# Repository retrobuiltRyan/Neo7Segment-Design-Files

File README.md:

KiCAD 8.x files created.

A reworked layout of Unexpected Maker's 7SegNeo Display project. Chain these addressable LED modules together to make a large 7-segment display. Control via any micro-controller just like you would control a strip of RGB LEDs. Custom library made by Unexpected Maker.

Assembly Required:
Each moduled has a resistor footprint at the Data In line. The first module in the chain requires a ~220-330 ohm resistor soldered here. Each moduled next in the chain requires this jumper closed; 0-ohm resistor or just a solder blob.

Change list: bumped-up passives footprint to 1206, finessed trace/ copper pour layout; slightly larger PCB area, larger mounting holes, decimal place pixel same footprint as all other pixels.
Created some 3D printable mounting brackets to expidite building projects like a clock/scoreboard. 

RGBLEDs: 1568-16347CT-ND or https://www.aliexpress.us/item/3256802466699315.html

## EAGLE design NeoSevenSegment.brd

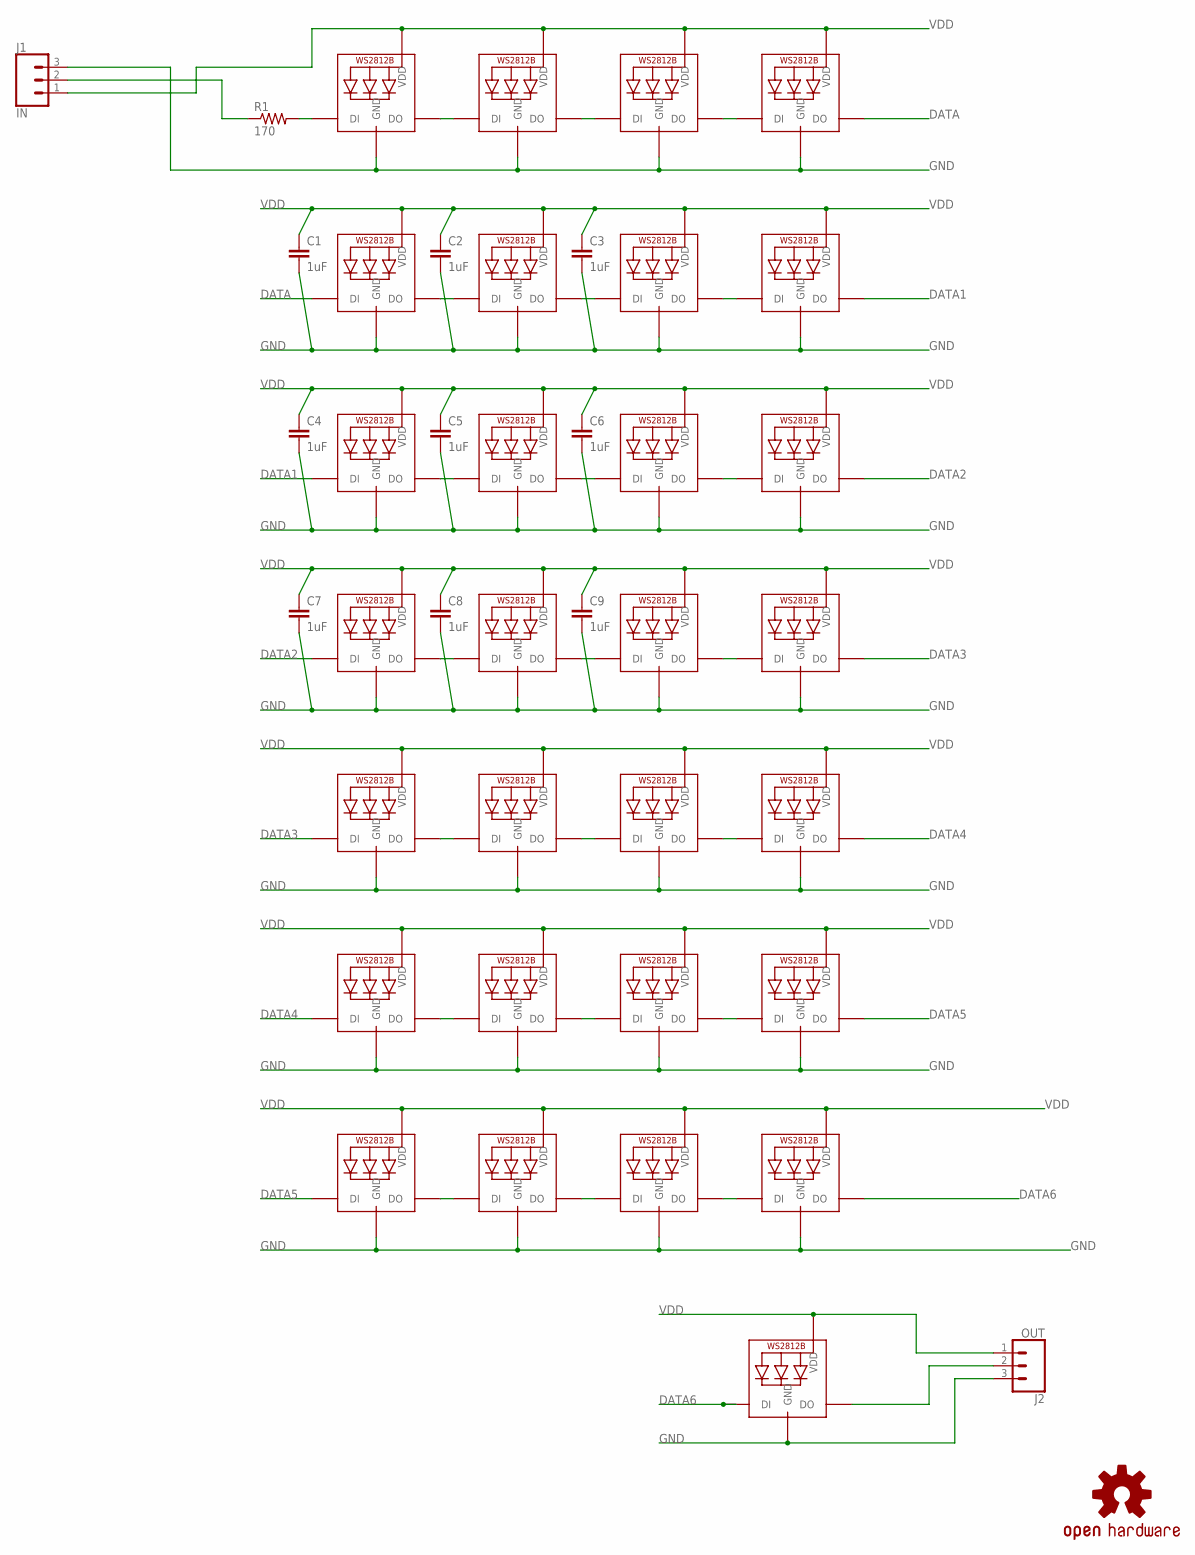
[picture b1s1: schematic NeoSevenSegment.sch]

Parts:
C1, C2, C3, C4, C5, C6, C7, C8, C9: 1uF; C1210
J1: IN; 1X03_LONGPADS
J2: OUT; 1X03_LONGPADS
LED1, LED2, LED3, LED4, LED5, LED6, LED7, LED8, LED9, LED10, LED11, LED12, LED13, LED14, LED15, LED16, LED17, LED18, LED19, LED20, LED21, LED22, LED23, LED24, LED25, LED26, LED27, LED28, LED29: WS2812B_5050N; WS2812B-NARROW
LOGO1: OSHW-LOGOM; OSHW-LOGO-M
R1: 170; R1206

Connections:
DATA: LED4.2-DOUT (DO), LED5.4-DIN (DI)
DATA1: LED8.2-DOUT (DO), LED9.4-DIN (DI)
DATA2: LED12.2-DOUT (DO), LED13.4-DIN (DI)
DATA3: LED16.2-DOUT (DO), LED17.4-DIN (DI)
DATA4: LED20.2-DOUT (DO), LED21.4-DIN (DI)
DATA5: LED24.2-DOUT (DO), LED25.4-DIN (DI)
DATA6: LED28.2-DOUT (DO), LED29.4-DIN (DI)
DATA_OUT: J2.2, LED29.2-DOUT (DO)
DI: J1.2, R1.1
DI_R: LED1.4-DIN (DI), R1.2
GND: C1.2, C2.2, C3.2, C4.2, C5.2, C6.2, C7.2, C8.2, C9.2, J1.3, J2.3, LED1.3-GND (GND), LED2.3-GND (GND), LED3.3-GND (GND), LED4.3-GND (GND), LED5.3-GND (GND), LED6.3-GND (GND), LED7.3-GND (GND), LED8.3-GND (GND), LED9.3-GND (GND), LED10.3-GND (GND), LED11.3-GND (GND), LED12.3-GND (GND), LED13.3-GND (GND), LED14.3-GND (GND), LED15.3-GND (GND), LED16.3-GND (GND), LED17.3-GND (GND), LED18.3-GND (GND), LED19.3-GND (GND), LED20.3-GND (GND), LED21.3-GND (GND), LED22.3-GND (GND), LED23.3-GND (GND), LED24.3-GND (GND), LED25.3-GND (GND), LED26.3-GND (GND), LED27.3-GND (GND), LED28.3-GND (GND), LED29.3-GND (GND)
unnamed: LED9.2-DOUT (DO), LED10.4-DIN (DI)
unnamed: LED10.2-DOUT (DO), LED11.4-DIN (DI)
unnamed: LED11.2-DOUT (DO), LED12.4-DIN (DI)
unnamed: LED1.2-DOUT (DO), LED2.4-DIN (DI)
unnamed: LED2.2-DOUT (DO), LED3.4-DIN (DI)
unnamed: LED3.2-DOUT (DO), LED4.4-DIN (DI)
unnamed: LED13.2-DOUT (DO), LED14.4-DIN (DI)
unnamed: LED14.2-DOUT (DO), LED15.4-DIN (DI)
unnamed: LED15.2-DOUT (DO), LED16.4-DIN (DI)
unnamed: LED17.2-DOUT (DO), LED18.4-DIN (DI)
unnamed: LED18.2-DOUT (DO), LED19.4-DIN (DI)
unnamed: LED5.2-DOUT (DO), LED6.4-DIN (DI)
unnamed: LED6.2-DOUT (DO), LED7.4-DIN (DI)
unnamed: LED7.2-DOUT (DO), LED8.4-DIN (DI)
unnamed: LED19.2-DOUT (DO), LED20.4-DIN (DI)
unnamed: LED21.2-DOUT (DO), LED22.4-DIN (DI)
unnamed: LED22.2-DOUT (DO), LED23.4-DIN (DI)
unnamed: LED23.2-DOUT (DO), LED24.4-DIN (DI)
S1: LED25.2-DOUT (DO), LED26.4-DIN (DI)
S2: LED26.2-DOUT (DO), LED27.4-DIN (DI)
S3: LED27.2-DOUT (DO), LED28.4-DIN (DI)
VDD: C1.1, C2.1, C3.1, C4.1, C5.1, C6.1, C7.1, C8.1, C9.1, J1.1, J2.1, LED1.1-VDD (VDD), LED2.1-VDD (VDD), LED3.1-VDD (VDD), LED4.1-VDD (VDD), LED5.1-VDD (VDD), LED6.1-VDD (VDD), LED7.1-VDD (VDD), LED8.1-VDD (VDD), LED9.1-VDD (VDD), LED10.1-VDD (VDD), LED11.1-VDD (VDD), LED12.1-VDD (VDD), LED13.1-VDD (VDD), LED14.1-VDD (VDD), LED15.1-VDD (VDD), LED16.1-VDD (VDD), LED17.1-VDD (VDD), LED18.1-VDD (VDD), LED19.1-VDD (VDD), LED20.1-VDD (VDD), LED21.1-VDD (VDD), LED22.1-VDD (VDD), LED23.1-VDD (VDD), LED24.1-VDD (VDD), LED25.1-VDD (VDD), LED26.1-VDD (VDD), LED27.1-VDD (VDD), LED28.1-VDD (VDD), LED29.1-VDD (VDD)

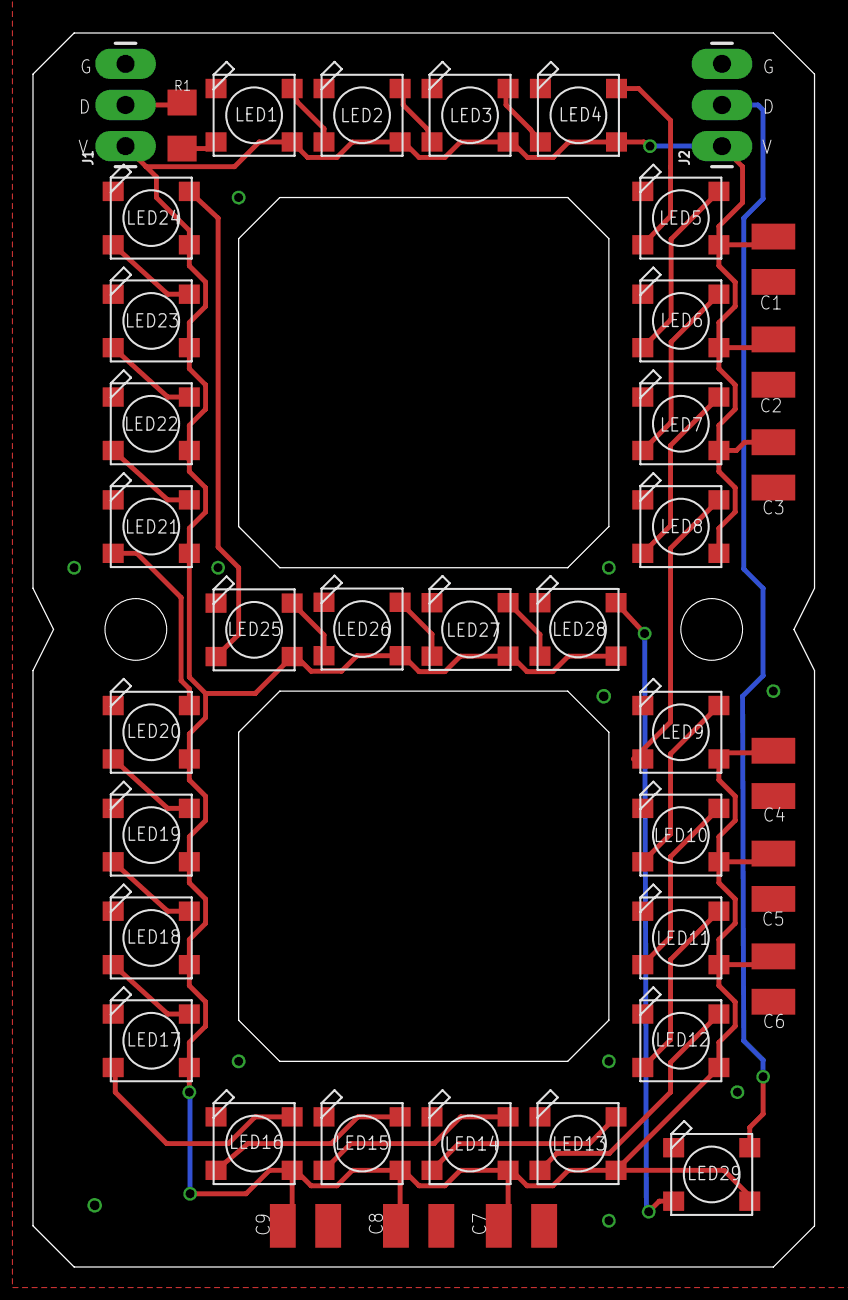
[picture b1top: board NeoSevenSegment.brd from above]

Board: 2 copper layers, 48.3 x 76.2 mm, 42 parts (1 on the bottom side), 33 nets.

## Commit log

2024-11-17 Eagle Design Files and Gerbers (ver Dec 2023)
2025-07-30 design Files
    July 2025 revision. big copper pours for VDD and GND.
2025-07-30 gerbers
2025-10-16 design Files
2025-10-16 gerbers
    JLCPCB tested
2025-10-17 Create LICENSE

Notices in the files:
parts and their libraries:
SparkFun-Connectors: Licensing: Creative Commons ShareAlike 4.0 International - https://creativecommons.org/licenses/by-sa/4.0
